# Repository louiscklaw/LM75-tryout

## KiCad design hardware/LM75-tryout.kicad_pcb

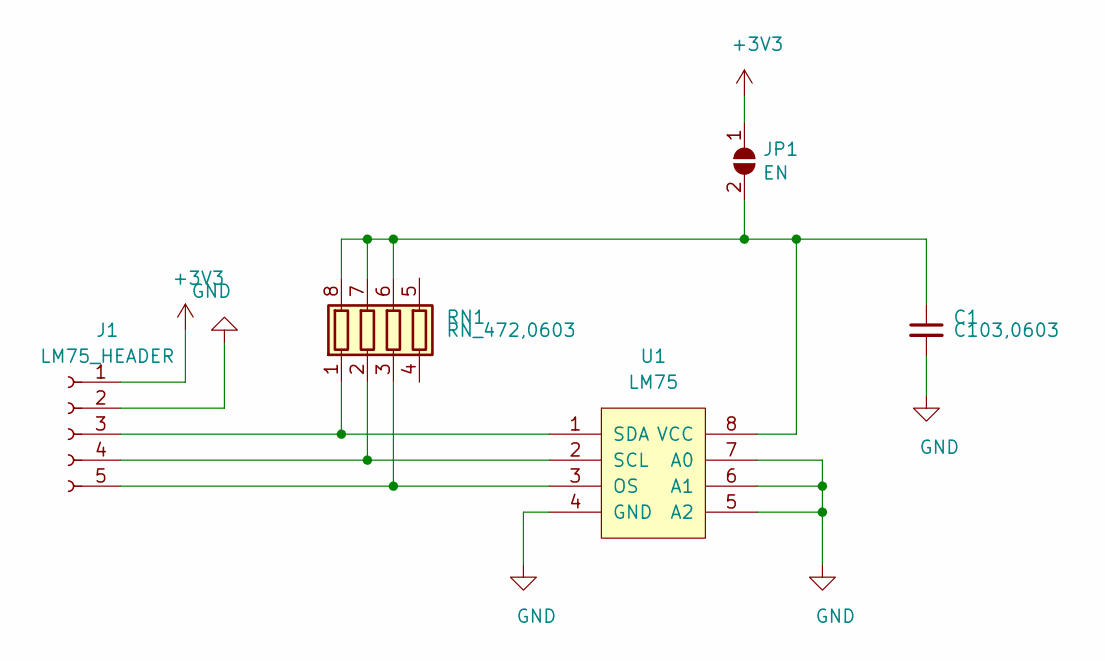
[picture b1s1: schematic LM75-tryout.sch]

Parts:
C1: C103,0603; C_0603_1608Metric_Pad1.05x0.95mm_HandSolder
J1: LM75_HEADER; PinHeader_1x05_P1.27mm_Vertical
JP1: EN; SolderJumper-2_P1.3mm_Open_RoundedPad1.0x1.5mm
RN1: RN_472,0603; R_Array_Concave_4x0603
U1: LM75; SOP-8_3.76x4.96mm_P1.27mm

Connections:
+3V3: J1.1, JP1.1 (A)
GND: C1.2, J1.2, U1.4 (GND), U1.5 (A2), U1.6 (A1), U1.7 (A0)
unnamed: C1.1, JP1.2 (B), RN1.6 (R3.2), RN1.7 (R2.2), RN1.8 (R1.2), U1.8 (VCC)
unnamed: J1.3, RN1.1 (R1.1), U1.1 (SDA)
unnamed: J1.4, RN1.2 (R2.1), U1.2 (SCL)
unnamed: J1.5, RN1.3 (R3.1), U1.3 (OS)

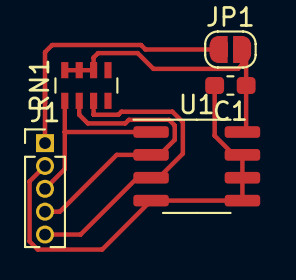
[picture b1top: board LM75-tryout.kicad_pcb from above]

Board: 2 copper layers, 5 parts (0 on the bottom side), 6 nets.

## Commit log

2019-05-30 update for layout,
2019-05-31 update,
2019-06-06 update for power led,
2020-05-06 ci: init travis build config,
2020-05-06 ci: init travis token,
